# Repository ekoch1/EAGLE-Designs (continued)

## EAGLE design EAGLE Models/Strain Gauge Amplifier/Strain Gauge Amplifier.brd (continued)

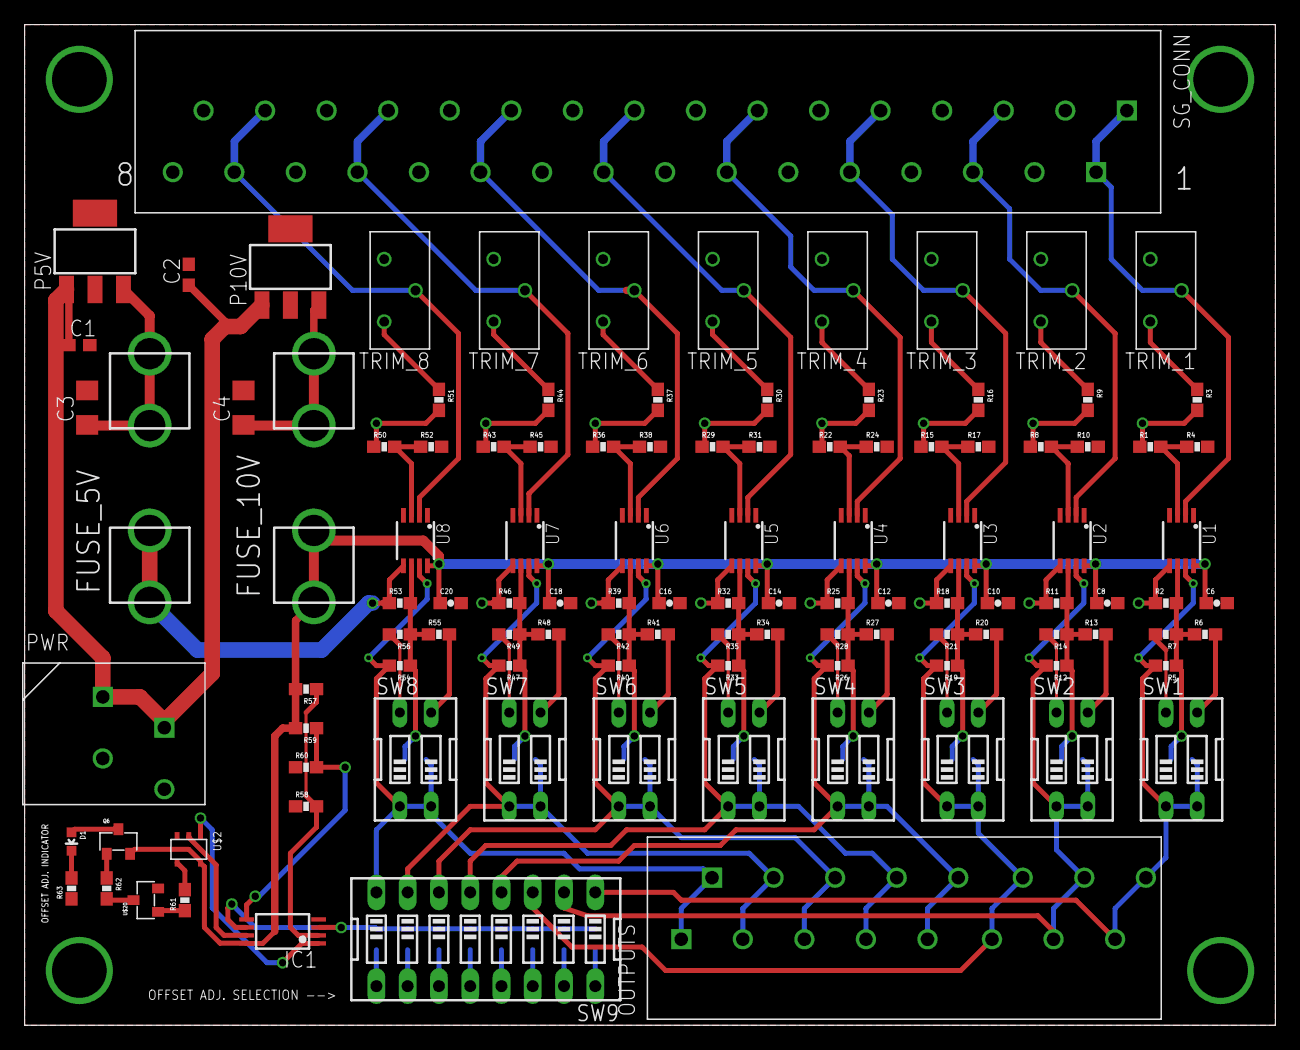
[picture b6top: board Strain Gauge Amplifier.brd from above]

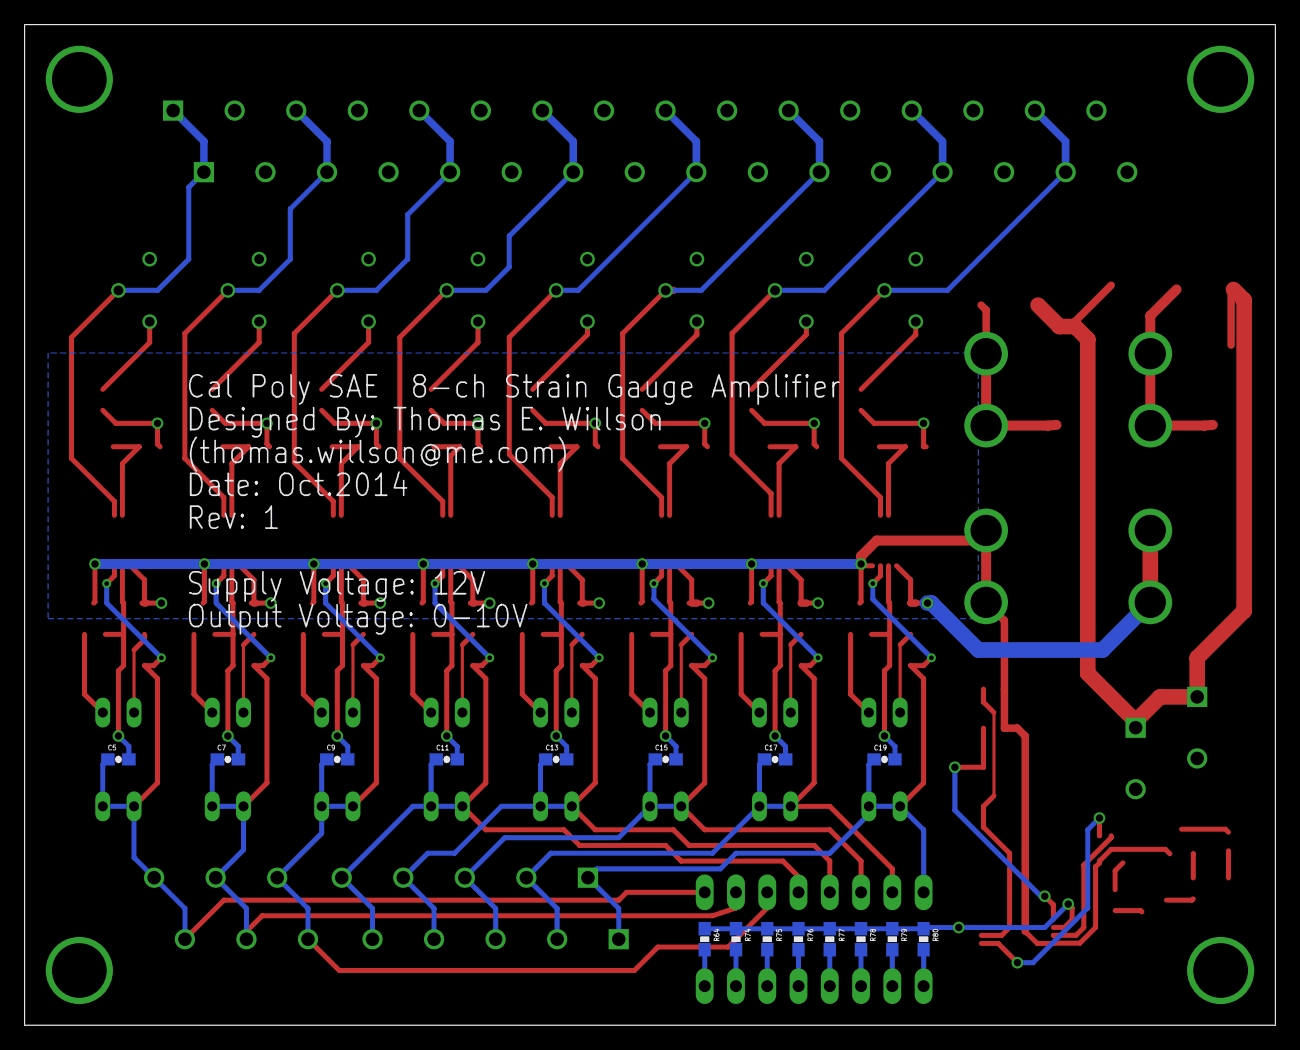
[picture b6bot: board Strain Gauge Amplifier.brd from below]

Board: 2 copper layers, 101.6 x 81.3 mm, 128 parts (16 on the bottom side), 81 nets.

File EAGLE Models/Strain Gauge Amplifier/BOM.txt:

Qty	Value	Device	Package	Parts	Description	PROD_ID	VALUE	Digikey8		SW_DIP-2	DIPSWITCH-02	"SW1, SW2, SW3, SW4, SW5, SW6, SW7, SW8"	DIP SWITCH			GH7200-ND1		SW_DIP-8	DIPSWITCH-08	SW9	DIP Switch 8 Position			GH7212-ND2	.1uF	C-USC0603	C0603	"C1, C2"	"CAPACITOR, American symbol"			16	.1uF	CAP0603-CAP	0603-CAP	"C5, C6, C7, C8, C9, C10, C11, C12, C13, C14, C15, C16, C17, C18, C19, C20"	Capacitor			2	1.6k	RESISTOR0603	0603-RES	"R58, R59"	Resistor			2	1.8k	RESISTOR0603	0603-RES	"R57, R60"	Resistor			1	10V	LM2937	SOT223	P10V				2	10uF	C-USC1206	C1206	"C3, C4"	"CAPACITOR, American symbol"			8	110k	RESISTOR0603	0603-RES	"R5, R12, R19, R26, R33, R40, R47, R54"	Resistor			24	1k	RESISTOR0603	0603-RES	"R1, R2, R4, R8, R10, R11, R15, R17, R18, R22, R24, R25, R29, R31, R32, R36, R38, R39, R43, R45, R46, R50, R52, R53"	Resistor			8	20	3296Y	"3926_Y,Z"	"TRIM_1, TRIM_2, TRIM_3, TRIM_4, TRIM_5, TRIM_6, TRIM_7, TRIM_8"	Trimpot			8	345	RESISTOR0603	0603-RES	"R3, R9, R16, R23, R30, R37, R44, R51"	Resistor			10	4.7k	RESISTOR0603	0603-RES	"R61, R62, R64, R74, R75, R76, R77, R78, R79, R80"	Resistor			1	430	RESISTOR0603	0603-RES	R63	Resistor			1	5V	LM2937	SOT223	P5V				8	62k	RESISTOR0603	0603-RES	"R6, R13, R20, R27, R34, R41, R48, R55"	Resistor			8	82k	RESISTOR0603	0603-RES	"R7, R14, R21, R28, R35, R42, R49, R56"	Resistor			1	CONN_16	CONN_16	CONNECTOR_16	SG_CONN				1	CONN_2	CONN_2	CONNECTOR_2	PWR				1	CONN_8	CONN_8	CONNECTOR_8	OUTPUTS				2	FUSEX20MM	FUSEX20MM	FUSE_5MM	"5V_FUSE, 10V_FUSE"				1	GREEN	LED-GREEN0603	LED-0603	D1	Various green LEDs	DIO-00821	GREEN	1	LM2903TSSOP	LM2903TSSOP	TSSOP8	IC1	COMPARATOR			8	LTC2053	LTC2053	MSOP8	"U1, U2, U3, U4, U5, U6, U7, U8"	DK: LTC2053CMS8#PBF-ND			1	MMBT4401-7-F	MMBT4401-7-F	SOT-23-3	U$20				1	MMBT4403-7-F	MMBT4403-7-F	SOT-23-3	Q6				1	TC4S81FT5LFT-AND_GATE	TC4S81FT5LFT-AND_GATE	SSOP5-P-0.95	U$2	TC4S81FT5LFTCT-ND

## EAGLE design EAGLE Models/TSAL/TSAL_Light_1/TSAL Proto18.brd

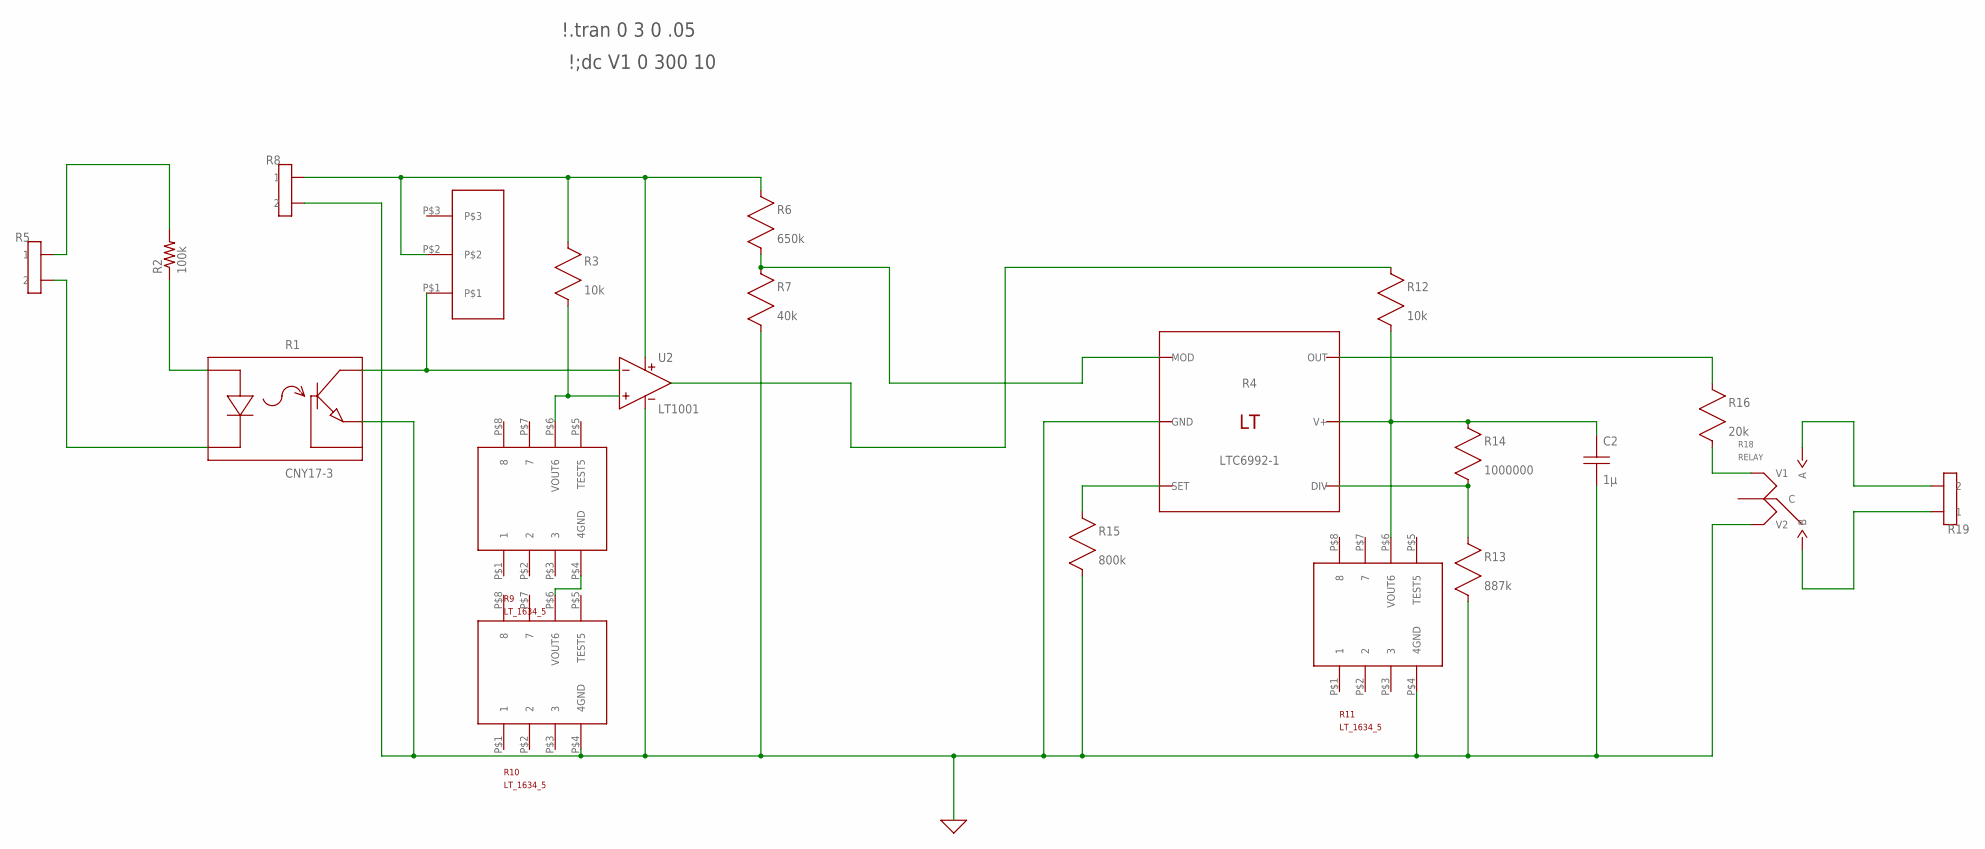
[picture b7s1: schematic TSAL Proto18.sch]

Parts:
C2: 1µ; C0805
R1: CNY17-3
R2: 100k; P0817/22
R3, R12: 10k; R0805
R4: LTC6992-1
R5, R8, R19: CONN_2; CONNECTOR_2
R6: 650k; R0805
R7: 40k; R0805
R9, R10, R11: LT_1634_5MS8; LT_1634_5
R13: 887k; R0805
R14: 1000000; R0805
R15: 800k; R0805
R16: 20k; R0805
R17: RK097111T
R18: RELAY
U2: LT1001; S8

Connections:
0: C2.2 (B), R1.P$4 (E), R4.P$2 (GND), R7.2 (B), R8.3 (2), R8.4 (2), R10.P$4 (4GND), R11.P$4 (4GND), R13.2 (B), R15.2 (B), R18.V2, U2.4 (V-)
unnamed: R2.2, R5.1, R5.2 (1)
unnamed: R1.P$2 (K), R5.3 (2), R5.4 (2)
unnamed: R9.P$4 (4GND), R10.P$6 (VOUT6)
unnamed: R3.1 (A), R6.1 (A), R8.1, R8.2 (1), R17.P$2, U2.8 (V+)
unnamed: R16.2 (B), R18.V1
unnamed: R12.1 (A), U2.3 (OUT)
unnamed: R4.P$1 (MOD), R6.2 (B), R7.1 (A)
unnamed: R4.P$6 (OUT), R16.1 (A)
unnamed: R1.P$1 (A), R2.1
unnamed: R1.P$5 (C), R17.P$1, U2.2 (IN-)
unnamed: R18.A, R19.3 (2), R19.4 (2)
unnamed: R3.2 (B), R9.P$6 (VOUT6), U2.1 (IN+)
unnamed: R18.B, R19.1, R19.2 (1)
unnamed: C2.1 (A), R4.P$5 (V+), R11.P$6 (VOUT6), R12.2 (B), R14.1 (A)
unnamed: R4.P$3 (SET), R15.1 (A)
unnamed: R4.P$4 (DIV), R13.1 (A), R14.2 (B)

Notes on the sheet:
\!;dc V1 0 300 10
\!.tran 0 3 0 .05

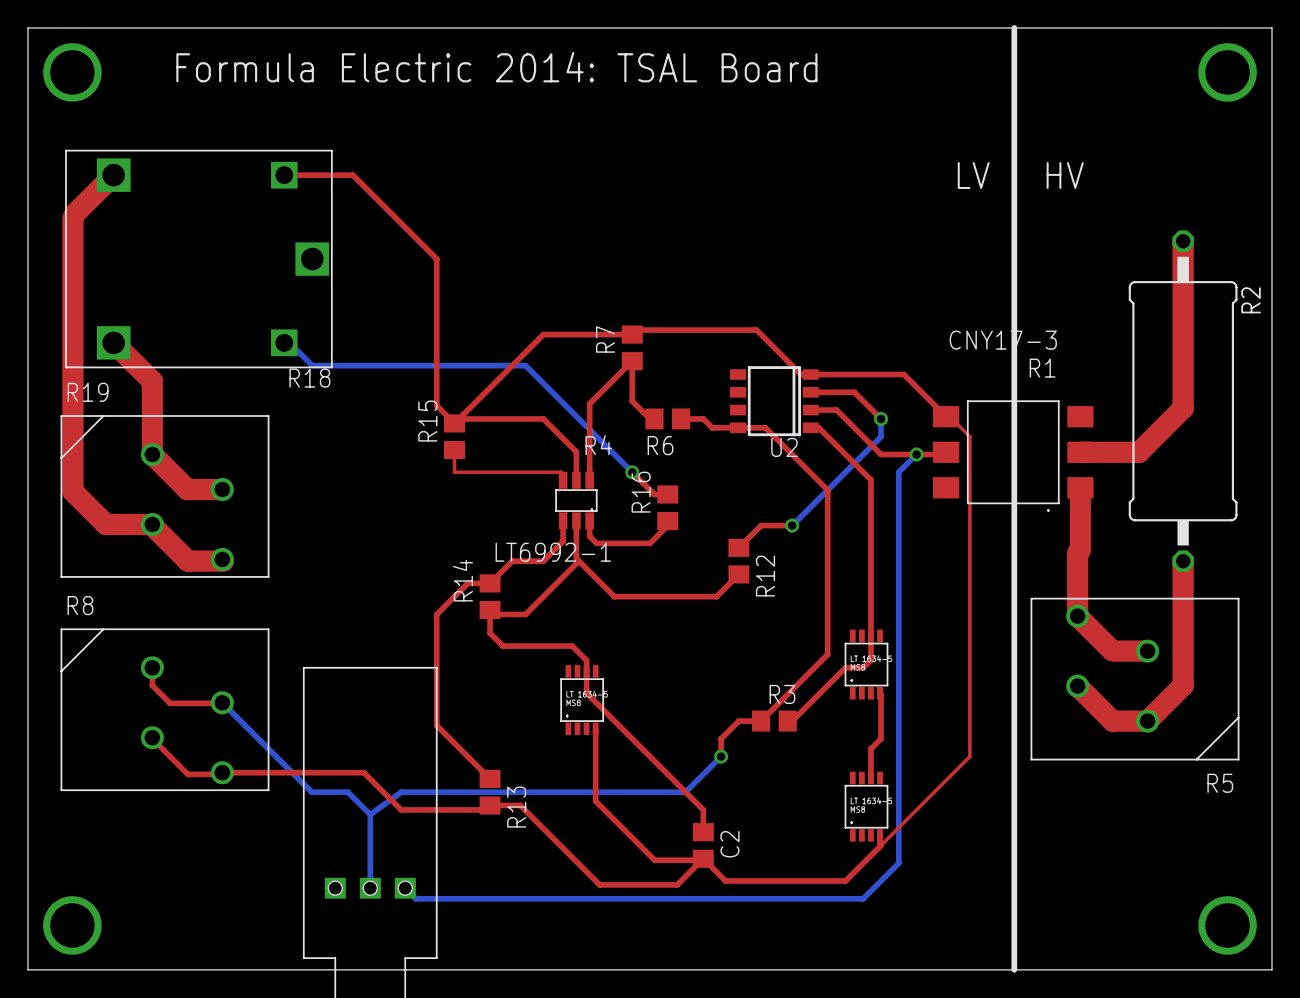
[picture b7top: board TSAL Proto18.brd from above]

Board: 2 copper layers, 88.9 x 67.3 mm, 21 parts (0 on the bottom side), 17 nets.
